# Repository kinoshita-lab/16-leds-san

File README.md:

# 16-LEDs-san

## PCB board with 16 NeoPixel LEDs

16-LEDs-san is a handy PCB with 16 cascaded neopixel-comapible LEDs.
You can also cascade same PCBs.
It is useful for the MCUs that have few GPIOs.

## Kit contents

- Pre-assembled circuit board
- 1x3 pin socket

## How to assemble

Solder the included 1x03 pin socket into the following place below:

## Sample program

There are no specific sample software for the PCB. Please refer to the NeoPixel software implementations.

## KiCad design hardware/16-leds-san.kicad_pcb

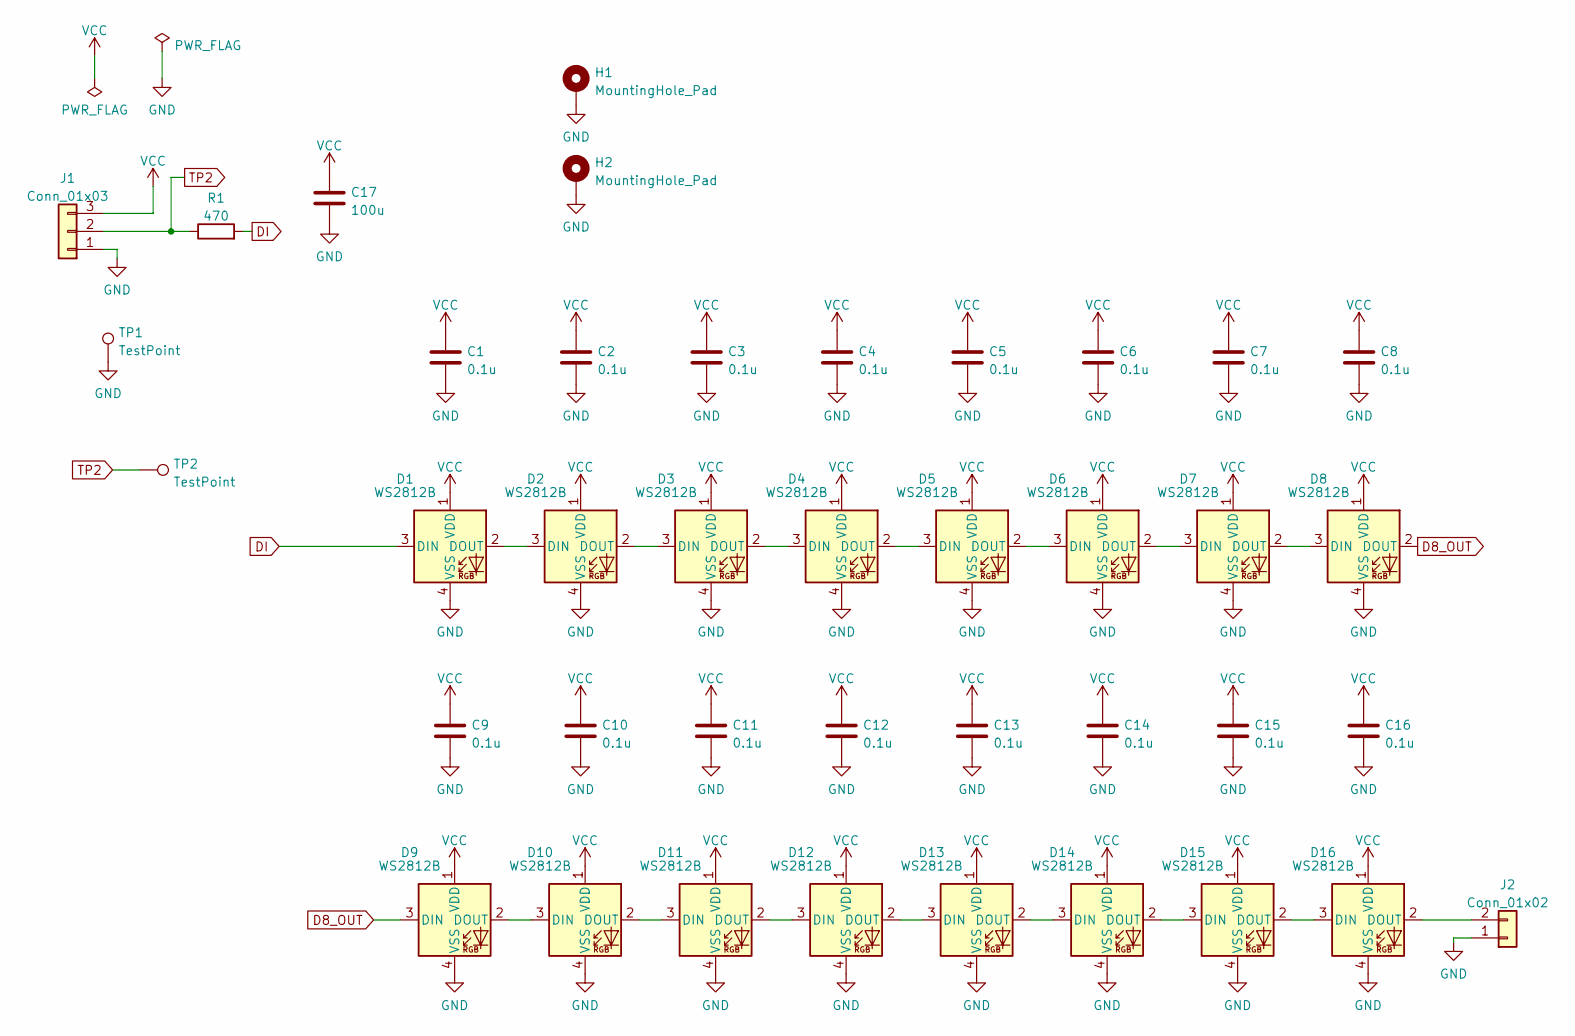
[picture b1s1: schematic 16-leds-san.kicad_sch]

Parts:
C1, C2, C3, C4, C5, C6, C7, C8, C9, C10, C11, C12, C13, C14, C15, C16: 0.1u; C_0402_1005Metric_Pad0.74x0.62mm_HandSolder; LCSC C1525
C17: 100u; C_1206_3216Metric_Pad1.33x1.80mm_HandSolder; LCSC C312983
D1, D2, D3, D4, D5, D6, D7, D8, D9, D10, D11, D12, D13, D14, D15, D16: WS2812B; LED_NeoPixel_XL-5050RGBC-WS2812B; LCSC C2843785
H1, H2: MountingHole_Pad; MountingHole_3.2mm_M3_DIN965_Pad
J1: Conn_01x03; PinHeader_1x03_P2.54mm_Vertical
J2: Conn_01x02; PinSocket_1x02_P2.54mm_Vertical
R1: 470; R_0402_1005Metric_Pad0.72x0.64mm_HandSolder; LCSC C25117
TP1, TP2: TestPoint; TestPoint_THTPad_D2.0mm_Drill1.0mm

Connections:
D8_OUT: D8.2 (DOUT), D9.3 (DIN)
DI: D1.3 (DIN), R1.2
GND: C1.2, C2.2, C3.2, C4.2, C5.2, C6.2, C7.2, C8.2, C9.2, C10.2, C11.2, C12.2, C13.2, C14.2, C15.2, C16.2, C17.2, D1.4 (VSS), D2.4 (VSS), D3.4 (VSS), D4.4 (VSS), D5.4 (VSS), D6.4 (VSS), D7.4 (VSS), D8.4 (VSS), D9.4 (VSS), D10.4 (VSS), D11.4 (VSS), D12.4 (VSS), D13.4 (VSS), D14.4 (VSS), D15.4 (VSS), D16.4 (VSS), H1.1, H2.1, J1.1, J2.1, TP1.1
unnamed: D1.2 (DOUT), D2.3 (DIN)
unnamed: D2.2 (DOUT), D3.3 (DIN)
unnamed: D3.2 (DOUT), D4.3 (DIN)
unnamed: D4.2 (DOUT), D5.3 (DIN)
unnamed: D5.2 (DOUT), D6.3 (DIN)
unnamed: D6.2 (DOUT), D7.3 (DIN)
unnamed: D7.2 (DOUT), D8.3 (DIN)
unnamed: D10.2 (DOUT), D11.3 (DIN)
unnamed: D9.2 (DOUT), D10.3 (DIN)
unnamed: D11.2 (DOUT), D12.3 (DIN)
unnamed: D12.2 (DOUT), D13.3 (DIN)
unnamed: D13.2 (DOUT), D14.3 (DIN)
unnamed: D14.2 (DOUT), D15.3 (DIN)
unnamed: D15.2 (DOUT), D16.3 (DIN)
unnamed: D16.2 (DOUT), J2.2
TP2: J1.2, R1.1, TP2.1
VCC: C1.1, C2.1, C3.1, C4.1, C5.1, C6.1, C7.1, C8.1, C9.1, C10.1, C11.1, C12.1, C13.1, C14.1, C15.1, C16.1, C17.1, D1.1 (VDD), D2.1 (VDD), D3.1 (VDD), D4.1 (VDD), D5.1 (VDD), D6.1 (VDD), D7.1 (VDD), D8.1 (VDD), D9.1 (VDD), D10.1 (VDD), D11.1 (VDD), D12.1 (VDD), D13.1 (VDD), D14.1 (VDD), D15.1 (VDD), D16.1 (VDD), J1.3

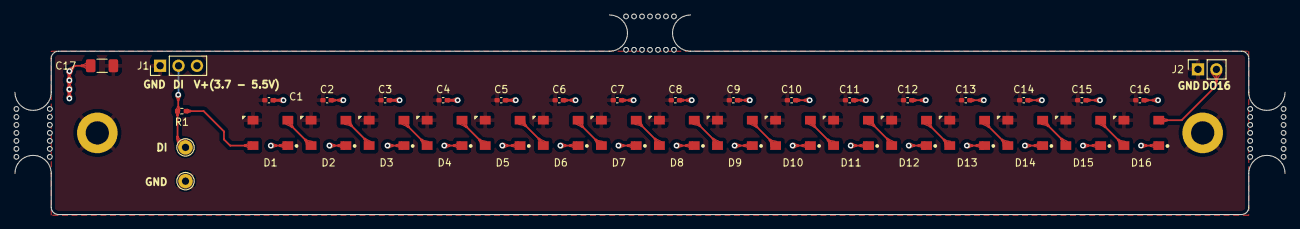
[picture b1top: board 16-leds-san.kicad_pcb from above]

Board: 2 copper layers, 175.0 x 27.5 mm, 40 parts (0 on the bottom side), 20 nets.

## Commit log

2022-08-24 add readme
2022-08-24 add readme_ja
2022-09-02 add doc
2022-09-02 add docs
2022-09-02 modify .gitignore
2022-09-02 add schematic
2022-09-02 add pcb pdf
2022-11-20 Create LICENSE
